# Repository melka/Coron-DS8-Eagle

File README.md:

# Coron DS8 Clone

Eagle project for the [Coron DS8 Clone by Marc Bareille](http://m.bareille.free.fr/ds7clone/ds8.htm)

[BOM on Mouser](http://www.mouser.com/ProjectManager/ProjectDetail.aspx?AccessID=e1b7458c28)

Block diagrams: 
http://m.bareille.free.fr/ds7clone/ds8_rev1_wiring1.gif

Original schematics:
http://m.bareille.free.fr/ds7clone/ds8_schem_rev1.pdf

### TODO
*   Add diode on power supply for reverse protection.

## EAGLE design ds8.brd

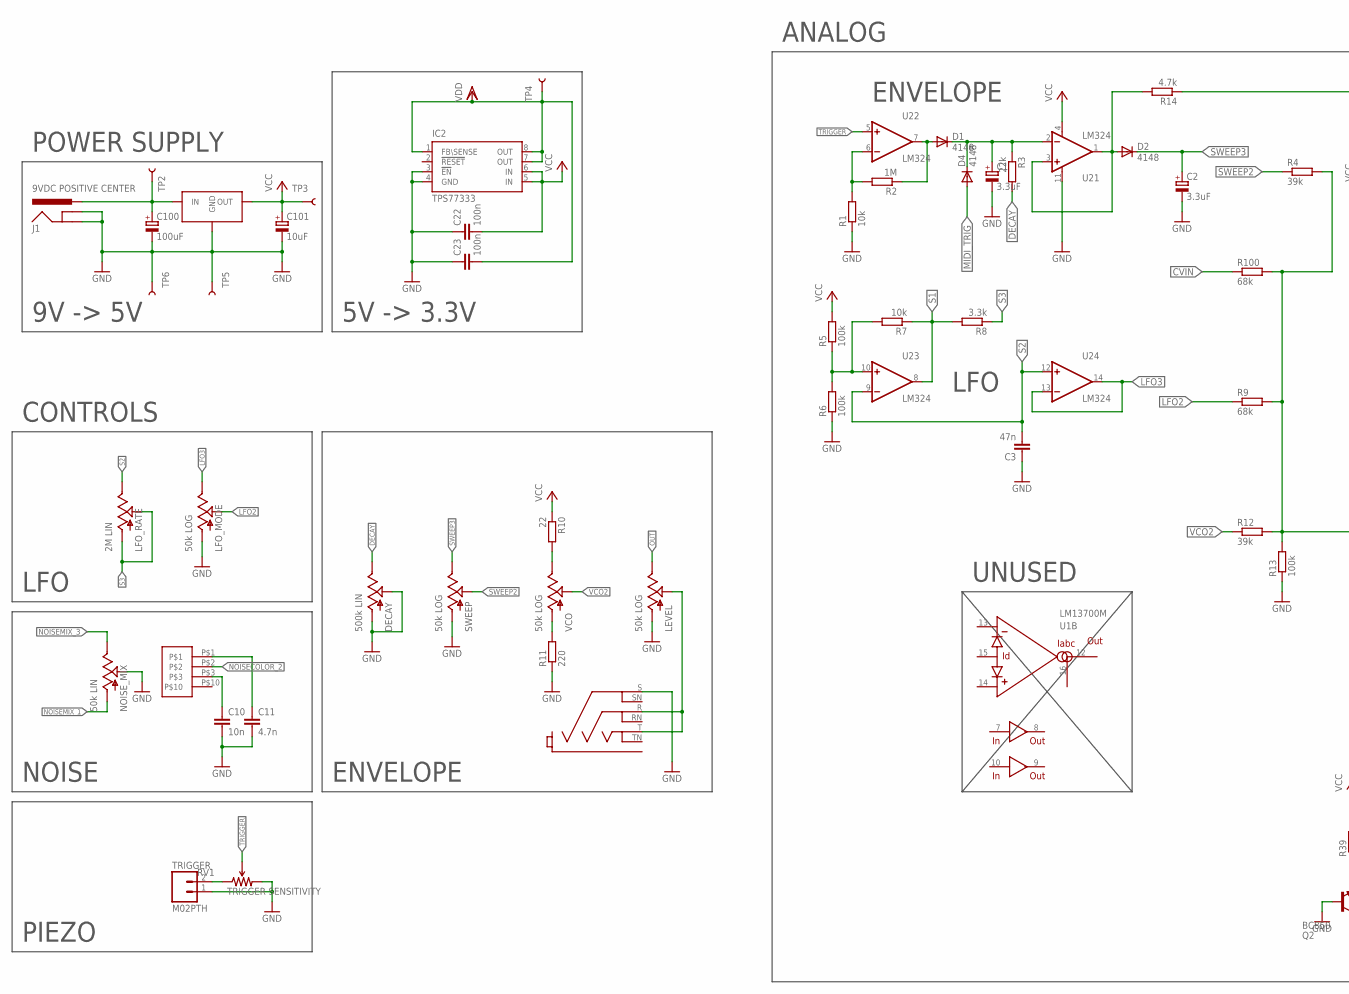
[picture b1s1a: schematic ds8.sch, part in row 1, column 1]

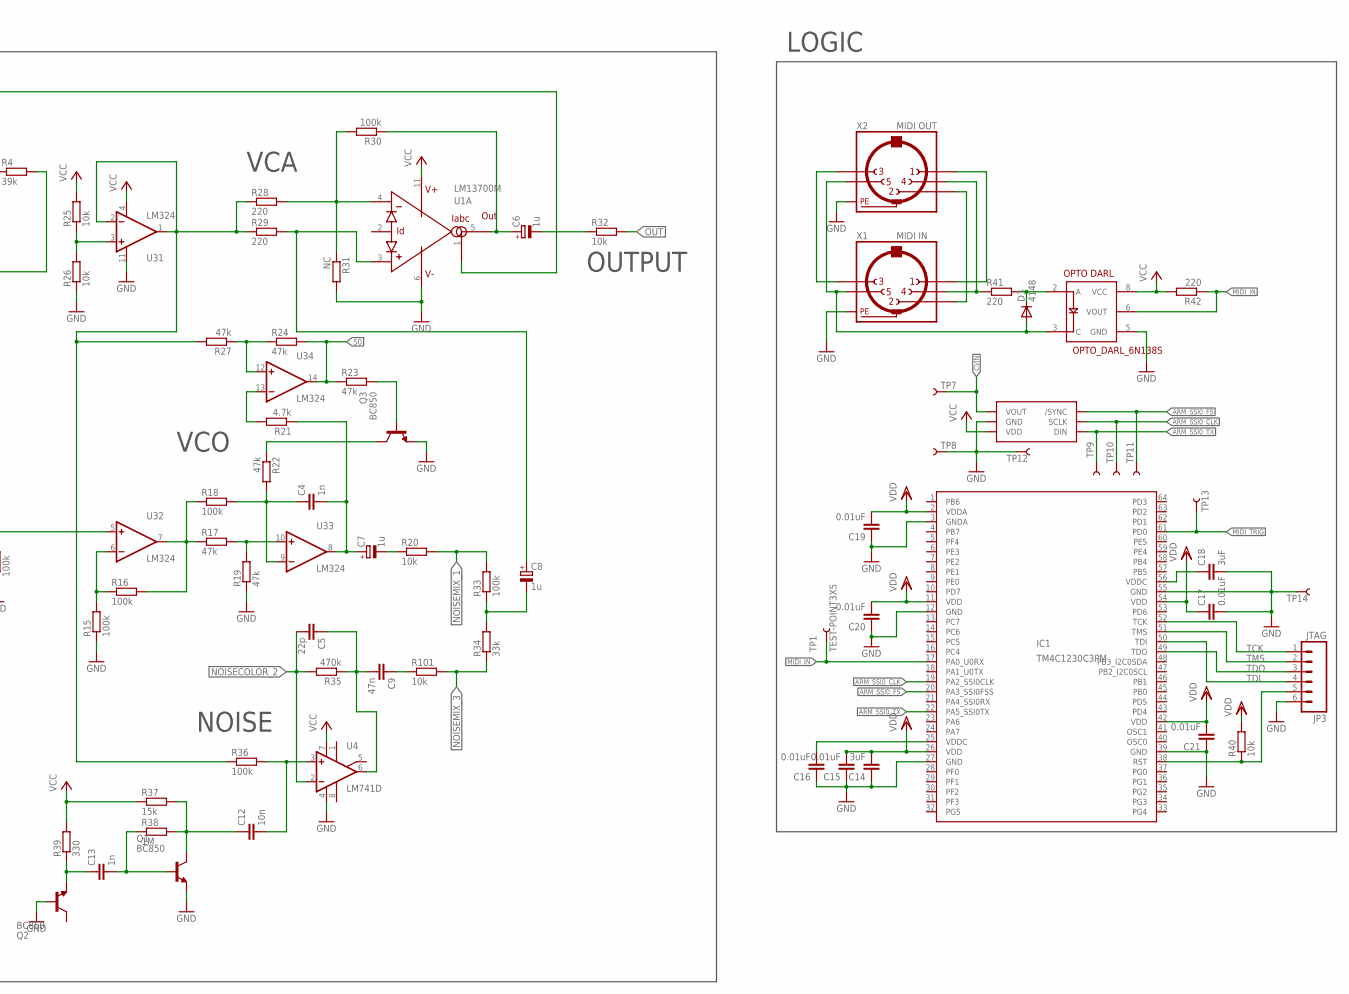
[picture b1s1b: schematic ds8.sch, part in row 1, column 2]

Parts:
C1, C2: 3.3uF; R/2012-12R
C3, C9: 47n; C1206
C4, C13: 1n; C1206
C5: 22p; C1206
C6, C7, C8: 1u; R/2012-12R
C10, C12: 10n; C1206
C11: 4.7n; C1206
C14, C18: 3uF; C1206
C15, C16, C17, C19, C20, C21: 0.01uF; C1206
C22, C23: 100n; C1206
C100: 100uF; PANASONIC_D
C101: 10uF; R/2012-12R
D1, D2, D3, D4: 4148; MINIMELF
DECAY: 500k LIN; ALPS_POT_KIT
IC1: TM4C1230C3PM; LQFP_64
IC2: TPS77333; SOP-08
IC3: DAC7512; SOT-23-6
J1: 9VDC POSITIVE CENTER; POWER_JACK_PTH_LOCK
JP3: JTAG; 1X06
LEVEL: 50k LOG; ALPS_POT_KIT
LFO_MODE: 50k LOG; ALPS_POT_KIT
LFO_RATE: 2M LIN; ALPS_POT_KIT
NOISE_MIX: 50k LIN; ALPS_POT_KIT
Q1, Q2, Q3: BC850; SOT23
R1, R7: 10k; R0805
R2: 1M; R0805
R3: 22k; R0805
R4, R12: 39k; R0805
R5, R6, R13, R15: 100k; R0805
R8: 3.3k; R0805
R9, R100: 68k; R0805
R10: 22; R0805
R11, R41, R42: 220; R0805
R14: 4.7k; R0805
R16, R18, R30, R33, R36: 100k; M0805
R17, R19, R22, R23, R24, R27: 47k; M0805
R20, R25, R26, R32, R40, R101: 10k; M0805
R21: 4.7k; M0805
R28, R29: 220; M0805
R31: NC; M0805
R34: 33k; M0805
R35: 470k; M0805
R37: 15k; M0805
R38: 1M; M0805
R39: 330; M0805
RV1: TRIGGER SENSITIVITY; TRIMPOT-5MM-V2
SWEEP: 50k LOG; ALPS_POT_KIT
TP1, TP2, TP3, TP4, TP5, TP6, TP7, TP8, TP9, TP10, TP11, TP12, TP13, TP14: TEST-POINT3X5; PAD.03X.05
TRIGGER: M02PTH; 1X02
U1: LM13700M; DS8_SO16
U2, U3: LM324; SOIC-14
U4: LM741D; SO08
U100: VREG-7805-DPAK2
U$1: 6.35MMJACK; NMJ6HCD3
U$3: ALPS_SRBV
U$4: OPTO_DARL_6N138S; 8-SMD
VCO: 50k LOG; ALPS_POT_KIT
X1: MIDI IN; MAB5SH
X2: MIDI OUT; MAB5SH

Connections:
9VDC: C100.+, J1.PWR, TP2.P$1, U100.VIN (IN)
ARM_SSI0_CLK: IC1.19 (PA2_SSI0CLK), IC3.5 (SCLK), TP10.P$1
ARM_SSI0_FS: IC1.20 (PA3_SSI0FSS), IC3.6 (/SYNC), TP11.P$1
ARM_SSI0_TX: IC1.22 (PA5_SSI0TX), IC3.4 (DIN), TP9.P$1
CVIN: IC3.1 (VOUT), R100.1, TP7.P$1
DECAY: DECAY.P$1 (E), R3.2
GND: C1.-, C2.-, C3.1, C10.2, C11.2, C14.1, C15.1, C16.1, C17.2, C18.2, C19.1, C20.1, C21.1, C22.1, C23.1, C100.-, C101.-, DECAY.P$2 (S), DECAY.P$3 (A), IC1.3 (GNDA), IC1.12 (GND), IC1.27 (GND), IC1.39 (GND), IC1.55 (GND), IC2.3 (!EN), IC2.4 (GND), IC3.2 (GND), J1.GND, J1.GNDBREAK, JP3.6, LEVEL.P$3 (A), LFO_MODE.P$3 (A), NOISE_MIX.P$2 (S), Q1.2 (E), Q2.1 (B), Q3.2 (E), R1.1, R6.1, R11.1, R13.1, R15.1, R19.1, R26.1, R31.2, RV1.C (CW), SWEEP.P$3 (A), TP5.P$1, TP6.P$1, TP8.P$1, TP12.P$1, TP14.P$1, TRIGGER.1, U1.6 (V-), U2.11 (V-), U3.11 (V-), U4.4 (V-), U100.GND, U$1.S, U$4.5 (GND), X1.PE, X1.PE@ (PE), X2.PE, X2.PE@ (PE)
LFO2: LFO_MODE.P$2 (S), R9.1
LFO3: LFO_MODE.P$1 (E), U2.13 (-IN), U2.14 (OUT)
MIDI_IN: IC1.17 (PA0_U0RX), R42.1, TP1.P$1, U$4.6 (VOUT)
MIDI_TRIG: D4.A, IC1.61 (PD0), TP13.P$1
unnamed: D1.A, R2.1, U2.7 (OUT)
unnamed: R1.2, R2.2, U2.6 (-IN)
unnamed: C1.+, D1.C, D4.C, R3.1, U2.2 (-IN)
unnamed: D2.A, R14.2, U2.1 (OUT), U2.3 (+IN)
unnamed: R5.1, R6.2, R7.2, U2.10 (+IN)
unnamed: X1.1, X2.1
unnamed: R15.2, R16.1, U3.6 (-IN)
unnamed: R4.2, R9.2, R12.2, R13.2, R100.2, U3.5 (+IN)
unnamed: R16.2, R17.1, R18.1, U3.7 (OUT)
unnamed: R17.2, R19.2, U3.10 (+IN)
unnamed: C4.1, R18.2, R22.2, U3.9 (-IN)
unnamed: C8.-, R33.1, R34.2
unnamed: C7.-, R20.1
unnamed: C4.2, C7.+, R21.1, U3.8 (OUT)
unnamed: Q3.3 (C), R22.1
unnamed: R21.2, U3.13 (-IN)
unnamed: R24.1, R27.1, U3.12 (+IN)
unnamed: R41.1, X1.4, X2.4
unnamed: Q3.1 (B), R23.2
unnamed: R27.2, R28.1, R29.1, R36.1, U3.1 (OUT), U3.2 (-IN)
unnamed: C9.1, R101.1
unnamed: R25.1, R26.2, U3.3 (+IN)
unnamed: R28.2, R30.2, R31.1, U1.4 (-IN)
unnamed: C8.+, R29.2, U1.3 (+IN)
unnamed: C6.-, R32.1
unnamed: D3.C, R41.2, U$4.2 (A)
unnamed: C6.+, R30.1, U1.5 (OUT)
unnamed: C5.1, C9.2, R35.1, U4.6 (OUT)
unnamed: C12.1, Q1.3 (C), R37.2, R38.2
unnamed: C12.2, R36.2, U4.3 (+IN)
unnamed: R14.1, U1.1 (IABC)
unnamed: C13.2, Q1.1 (B), R38.1
unnamed: C13.1, Q2.2 (E), R39.1
unnamed: RV1.A (CCW), TRIGGER.2
unnamed: D3.A, U$4.3 (C), X1.5, X2.5
unnamed: C18.1, IC1.56 (VDDC)
unnamed: R10.2, VCO.P$1 (E)
unnamed: R11.2, VCO.P$3 (A)
unnamed: C10.1, U$3.P$3
unnamed: C11.1, U$3.P$1
unnamed: X1.2, X2.2
unnamed: C16.2, IC1.25 (VDDC)
unnamed: X1.3, X2.3
unnamed: LEVEL.P$2 (S), U$1.R, U$1.T
NOISECOLOR_2: C5.2, R35.2, U4.2 (-IN), U$3.P$2
NOISEMIX_1: NOISE_MIX.P$3 (A), R20.2, R33.2
NOISEMIX_3: NOISE_MIX.P$1 (E), R34.1, R101.2
OUT: LEVEL.P$1 (E), R32.2
RST: IC1.38 (RST), JP3.5, R40.1
S0: R23.1, R24.2, U3.14 (OUT)
S1: R7.1, R8.2, U2.8 (OUT)
S2: C3.2, LFO_RATE.P$1 (E), U2.9 (-IN), U2.12 (+IN)
S3: LFO_RATE.P$2 (S), LFO_RATE.P$3 (A), R8.1
SWEEP2: R4.1, SWEEP.P$2 (S)
SWEEP3: C2.+, D2.C, SWEEP.P$1 (E)
TCK: IC1.52 (TCK), JP3.1
TDI: IC1.50 (TDI), JP3.4
TDO: IC1.49 (TDO), JP3.3
TMS: IC1.51 (TMS), JP3.2
TRIGGER: RV1.B (WIPER), U2.5 (+IN)
VCC: C22.2, C101.+, IC2.5 (IN), IC2.6 (IN), IC3.3 (VDD), R5.2, R10.1, R25.2, R37.1, R39.2, R42.2, TP3.P$1, U1.11 (V+), U2.4 (V+), U3.4 (V+), U4.7 (V+), U100.VOUT (OUT), U$4.8 (VCC)
VCO2: R12.1, VCO.P$2 (S)
VDD: C14.2, C15.2, C17.1, C19.2, C20.2, C21.2, C23.2, IC1.2 (VDDA), IC1.11 (VDD), IC1.26 (VDD), IC1.42 (VDD), IC1.54 (VDD), IC2.1 (FB\SENSE), IC2.7 (OUT), IC2.8 (OUT), R40.2, TP4.P$1

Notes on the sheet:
ENVELOPE
VCA
OUTPUT
NOISE
VCO
LFO
CONTROLS
PIEZO
POWER SUPPLY
9V -> 5V
5V -> 3.3V
LOGIC
UNUSED
ANALOG

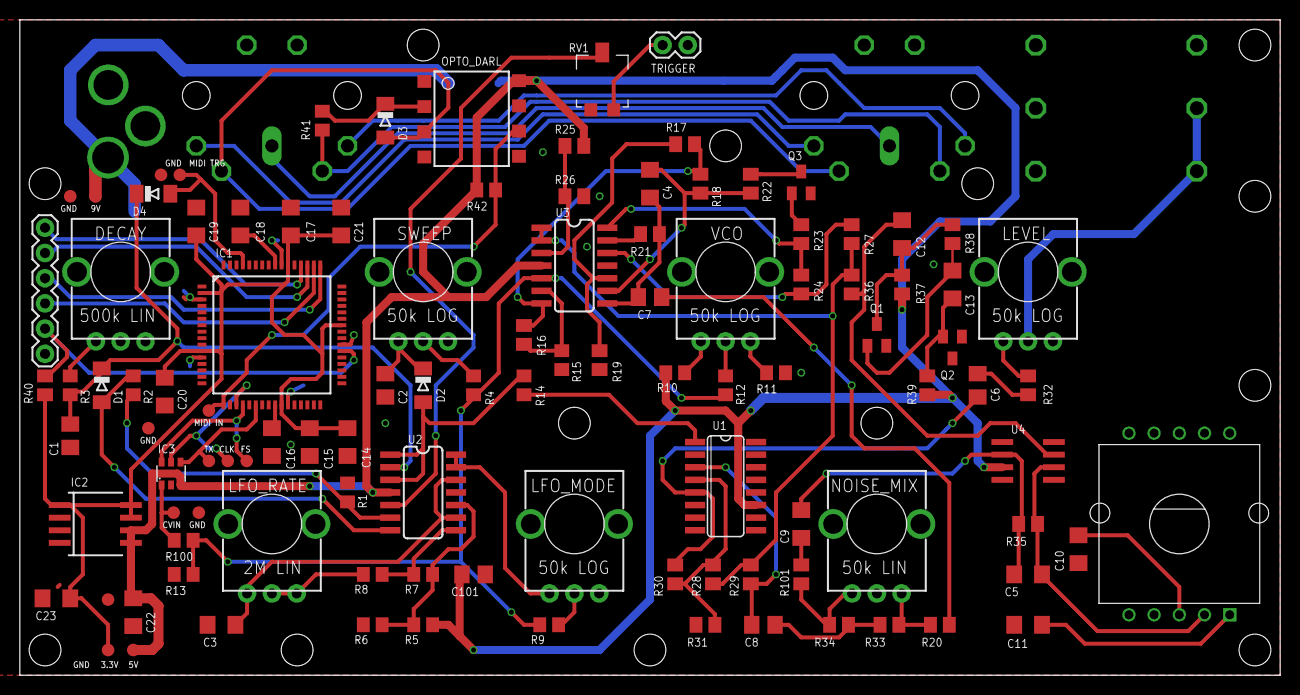
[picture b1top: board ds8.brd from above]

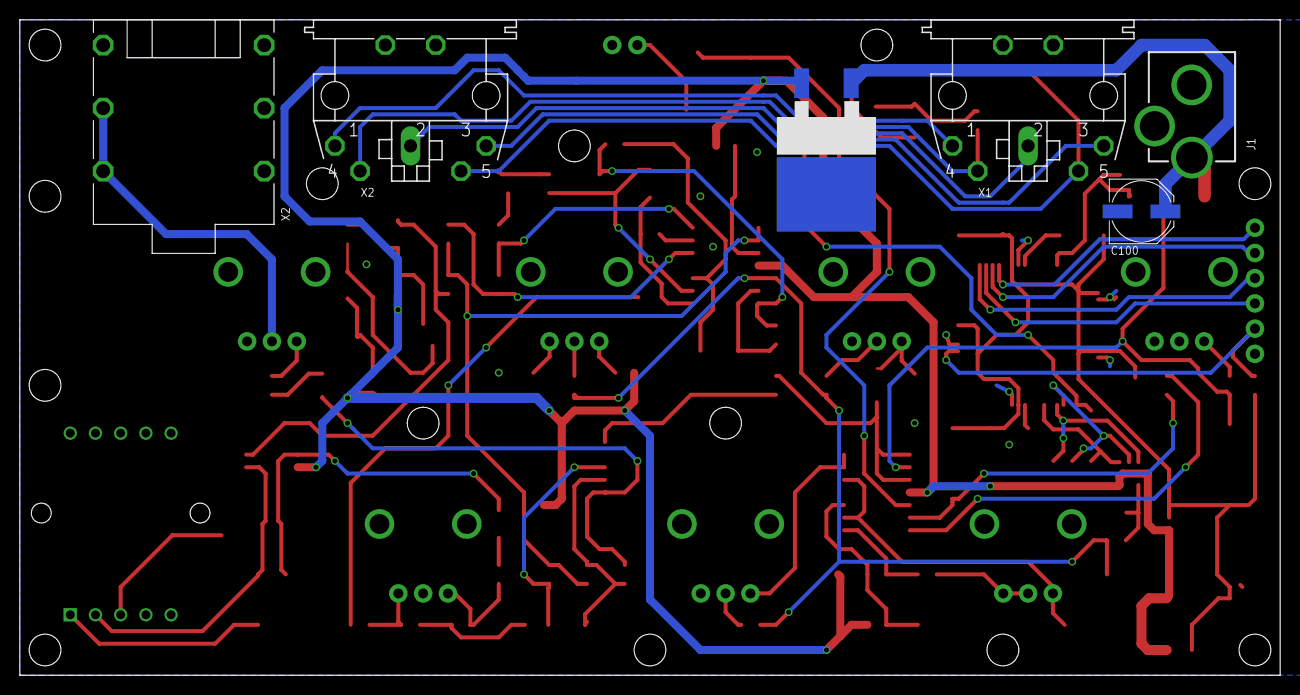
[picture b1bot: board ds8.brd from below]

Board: 4 copper layers, 127.0 x 66.0 mm, 114 parts (6 on the bottom side), 74 nets.

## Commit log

2014-02-12 Added README and link to BOM on Mouser
2014-02-12 added some text infos
2014-02-13 added regulator for mcu
2014-02-13 added dac
2014-02-13 clean up
2014-02-13 wire conflicts
2014-02-14 added optocoupler
2014-02-14 added SW debug on midi connector
2014-02-14 added midi trigger
2014-02-17 Board retouted
    - Cleaned the schematic
    - Board rerouted with through hole pots and new connectors
    - Lots of little stuff
2014-02-17 resistor upside down
2014-03-02 added more decoupling to vdd pins. jtag in place with a reset line
2014-03-18 TODO : Check JTAG
    Don't we need to have at least a common ground for the JTAG connection ? What about using this kind of supposedly standard header ? http://www.keil.com/support/man/docs/ulinkpro/ulinkpro_hw_if_jtag10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
    Done : board rerouted, added test points, added screw holes, moved a few things around, almost ready to be produced once we are sure about the JTAG stuff & checked the components one last time.
2014-03-20 Mech design revisions
    Moved screw holes and some little components for assembly
2014-04-03 PCB v1 Release
    Added GND on JTAG and a MIDI Passthrough connector
2014-07-03 Prototype v1
    Version that has been produced via Seeed Studio.
    Added todolist to readme.md.
2014-07-03 Previous commit mangled up the board file, here it is again. Not exactly the board used for prototyping but same functionnality.

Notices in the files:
parts and their libraries:
SparkFun-Electromechanical: Licensing: CC v3.0 Share-Alike You are welcome to use this library for commercial purposes.
